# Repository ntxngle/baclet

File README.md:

# baclet
## What and Why

A mobile, battery powered trinket that measures BAC (Blood AlcoholContent) by tracking time and drinks you enter via the extraordinarly user friendly triple button system.

Obviously this is not a medical device. You input body params on setup, then can log each drink by volume and percentage, and it calculates BAC. It has chargering, a buzzer, USB serial, and a nice 1.28 OLED, all behind an auto-off switch to save power.

Being the science minded individual I am, I have always approached consumption of this nature from a data driven mindset: I logged, sometimes more honestly than others, my drinks, and monitored my BAC level in the app. While I wouldn't say this pastime is exactly a hobby or passion, it's a part of my life and I figured it would be fun to try to connect the two disciplines. Thats why I made this brilliant contraption.

## Photos

## How it works
Again to be clear this is not a breathalyzer. You enter the drinks manually. Then, based parameters you've entered like weight, gender, it calculates the BAC level via the widmark formula. 

Drink inputs are timestamped from RTC and put into flash storage so it can be access and included in calculations on wake.

It was designed to be a thin as possible, with all SMD compontents located on one side, and the screen and buttons on the other. Barring the battery, this could have easily been a centimeter wide, but of course I'm not apple and cannot afford a custom designed battery to fit in the free space perfectly. I'm quite proud of the PCB design however, its pretty compact for the time it took me to make.

## BOM
|name                |quantity|Footprint                                         |link                                                |Price|
|--------------------|--------|--------------------------------------------------|----------------------------------------------------|-----|
|PCB                 |1       |                                                  |JLC files in repo                                   |2    |
|Battery             |1       |                                                  |https://es.aliexpress.com/item/1005012320035574.html|6    |
|Case                |1       |                                                  |3d print it                                         |1    |
|PCF8523T            |1       |SOIC-8_3.9x4.9mm_P1.27mm                          |https://www.lcsc.com/product-detail/C2651516.html   |1.19 |
|100k                |8       |R_0603_1608Metric                                 |https://www.lcsc.com/product-detail/C2906980.html   |0.38 |
|RP2040              |1       |QFN-56-1EP_7x7mm_P0.4mm_EP3.2x3.2mm               |https://www.lcsc.com/product-detail/C2040.html      |0.99 |
|1N4148              |3       |D_SOD-323F                                        |https://www.lcsc.com/product-detail/C2128.html      |0.59 |
|TPS63900            |1       |WSON-10-1EP_2.5x2.5mm_P0.5mm_EP1.2x2mm_ThermalVias|https://www.lcsc.com/product-detail/C1518762.html   |1.21 |
|W25Q32JVSS          |1       |SOIC-8_5.3x5.3mm_P1.27mm                          |https://www.lcsc.com/product-detail/C179173.html    |2.49 |
|NPN C22400355       |4       |SOT-23                                            |https://www.lcsc.com/product-detail/C22400355.html  |0.55 |
|2169900002          |1       |USB-SMD_2169900002                                |https://www.lcsc.com/product-detail/C3197869.html   |1.38 |
|2.2uH SRN3015TA-2R2M|1       |L_APV_ANR3010                                     |https://www.lcsc.com/product-detail/C5362464.html   |0.61 |
|C20625731           |1       |Crystal_SMD_3225-4Pin_3.2x2.5mm                   |https://www.lcsc.com/product-detail/C20625731.html  |1.47 |
|USBLC6-2SC6         |1       |SOT-23-6                                          |https://www.lcsc.com/product-detail/C7519.html      |0.87 |
|MLT-5020            |1       |BUZ-SMD_L5.0-W5.5-P4.60                           |https://www.lcsc.com/product-detail/C94598.html     |0.44 |
|MCP73831-2-OT       |1       |SOT-23-5                                          |https://www.lcsc.com/product-detail/C635037.html    |1.58 |
|B3F-1052            |3       |KEY-TH_4P-L6.0-W6.0-P4.50                         |https://www.lcsc.com/product-detail/C87037.html     |0.92 |
|HS13L03W2C01        |1       |OLED-TH_L35.4-W33.5_HS13L03W2C01                  |https://www.lcsc.com/product-detail/C7465997.html   |4.98 |
|Total               |        |                                                  |                                                    |32.54|

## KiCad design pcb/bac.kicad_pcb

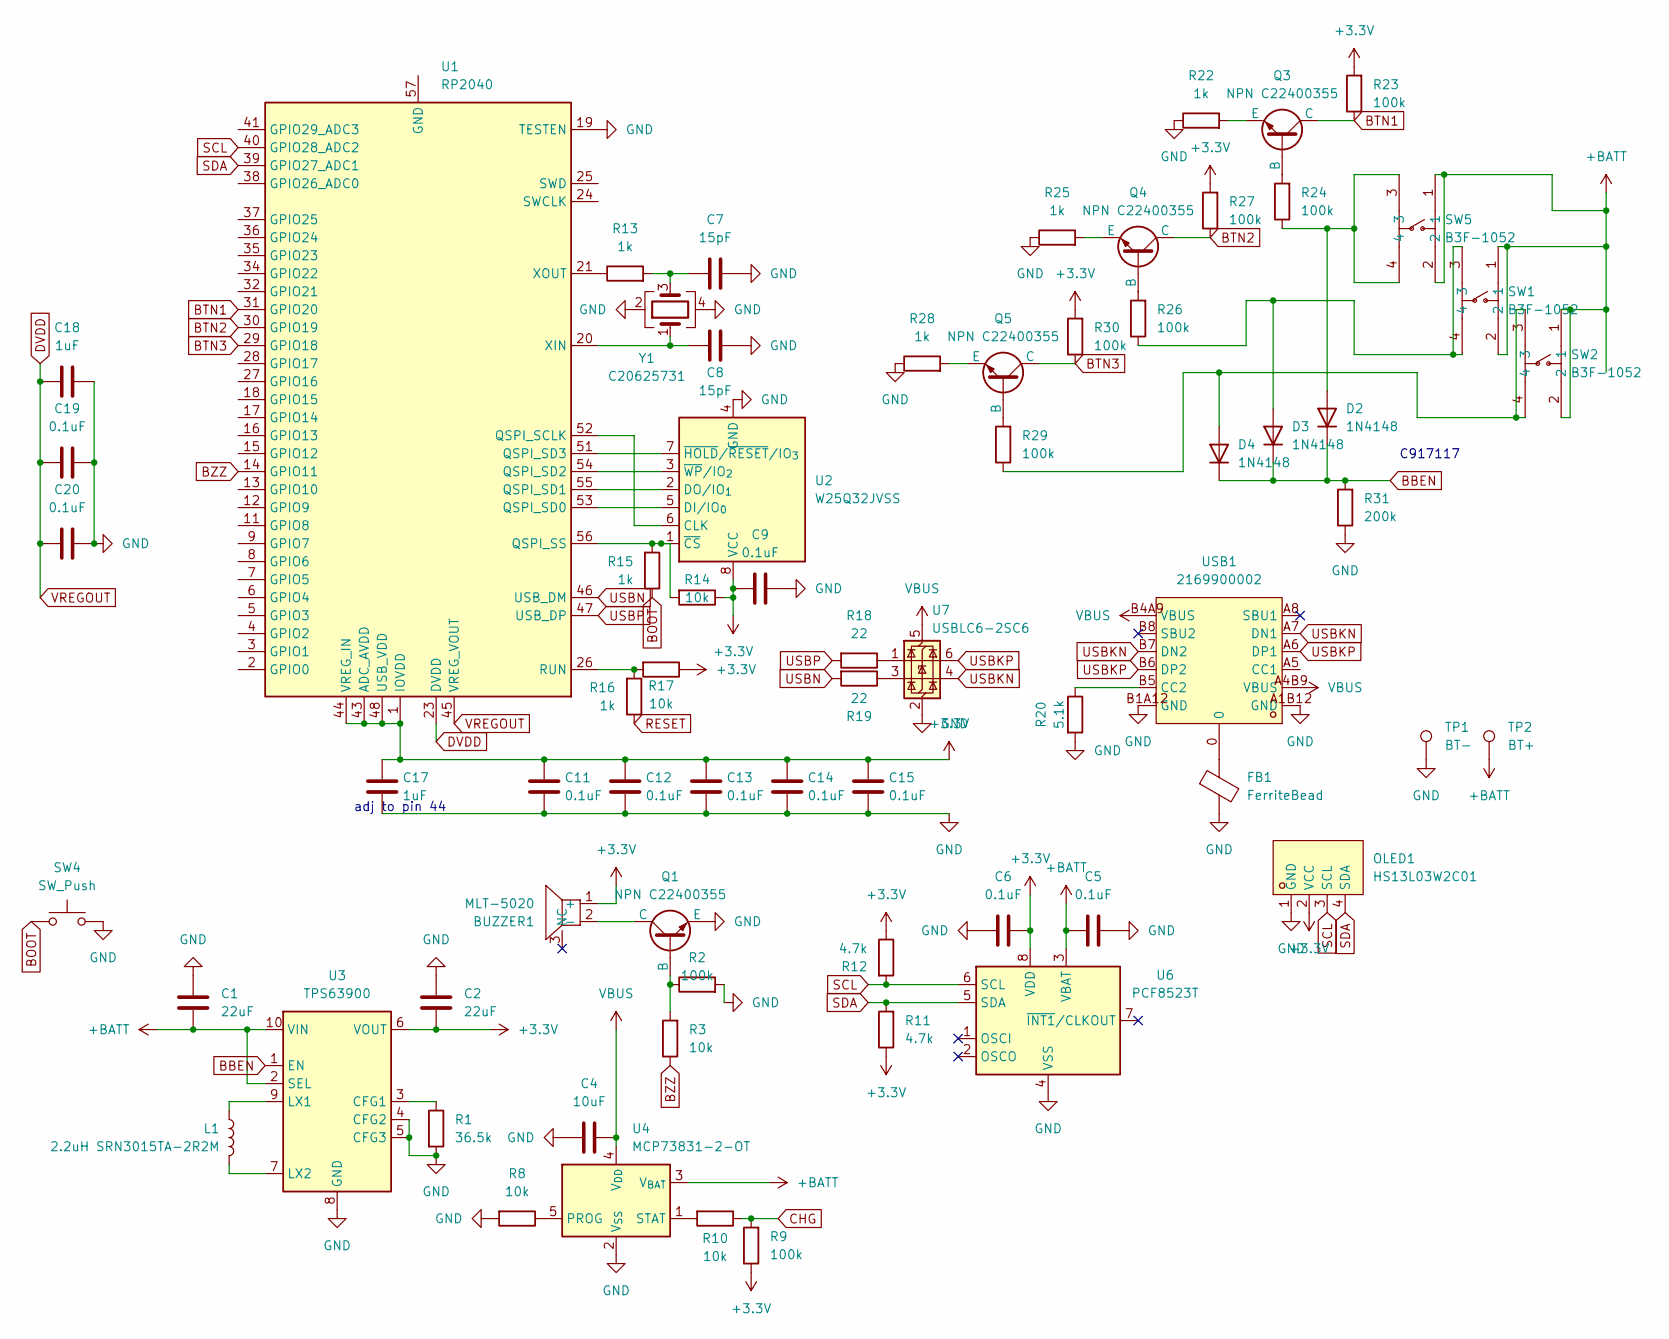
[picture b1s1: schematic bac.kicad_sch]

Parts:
BUZZER1: MLT-5020; BUZ-SMD_L5.0-W5.5-P4.60; MPN MLT-5020; LCSC Part C94598
C1, C2: 22uF; C_0603_1608Metric
C4: 10uF; C_0603_1608Metric
C5, C6, C9, C11, C12, C13, C14, C15, C19, C20: 0.1uF; C_0603_1608Metric
C7, C8: 15pF; C_0603_1608Metric
C17, C18: 1uF; C_0603_1608Metric
D2, D3, D4: 1N4148; D_SOD-323F
FB1: FerriteBead; L_0603_1608Metric
L1: 2.2uH SRN3015TA-2R2M; L_APV_ANR3010
OLED1: HS13L03W2C01; OLED-TH_L35.4-W33.5_HS13L03W2C01; MPN HS13L03W2C01; LCSC Part C7465997
Q1, Q3, Q4, Q5: NPN C22400355; SOT-23
R1: 36.5k; R_0603_1608Metric
R2, R9, R23, R24, R26, R27, R29, R30: 100k; R_0603_1608Metric
R3, R8, R10, R14, R17: 10k; R_0603_1608Metric
R11, R12: 4.7k; R_0603_1608Metric
R13, R15, R16, R22, R25, R28: 1k; R_0603_1608Metric
R18, R19: 22; R_0603_1608Metric
R20: 5.1k; R_0603_1608Metric
R31: 200k; R_0603_1608Metric
SW1, SW2, SW5: B3F-1052; KEY-TH_4P-L6.0-W6.0-P4.50; MPN B3F-1052; LCSC Part C87037
SW4: SW_Push
TP1: BT-; TestPoint_THTPad_2.0x2.0mm_Drill1.0mm
TP2: BT+; TestPoint_THTPad_2.0x2.0mm_Drill1.0mm
U1: RP2040; QFN-56-1EP_7x7mm_P0.4mm_EP3.2x3.2mm
U2: W25Q32JVSS; SOIC-8_5.3x5.3mm_P1.27mm
U3: TPS63900; WSON-10-1EP_2.5x2.5mm_P0.5mm_EP1.2x2mm_ThermalVias
U4: MCP73831-2-OT; SOT-23-5
U6: PCF8523T; SOIC-8_3.9x4.9mm_P1.27mm
U7: USBLC6-2SC6; SOT-23-6
USB1: 2169900002; USB-SMD_2169900002; MPN 2169900002; LCSC Part C3197869
Y1: C20625731; Crystal_SMD_3225-4Pin_3.2x2.5mm

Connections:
+3.3V: BUZZER1.1 (+), C2.1, C6.1, C9.2, C11.1, C12.1, C13.1, C14.1, C15.1, C17.1, OLED1.2 (VCC), R9.1, R11.1, R12.1, R14.1, R17.1, R23.2, R27.2, R30.2, U1.1 (IOVDD), U1.10 (IOVDD), U1.22 (IOVDD), U1.33 (IOVDD), U1.42 (IOVDD), U1.43 (ADC_AVDD), U1.44 (VREG_IN), U1.48 (USB_VDD), U1.49 (IOVDD), U2.8 (VCC), U3.6 (VOUT), U6.8 (VDD)
+BATT: C1.1, C5.2, SW1.1, SW1.2, SW2.1, SW2.2, SW5.1, SW5.2, TP2.1, U3.2 (SEL), U3.10 (VIN), U4.3 (V_{BAT}), U6.3 (VBAT)
BBEN: D2.1 (K), D3.1 (K), D4.1 (K), R31.2, U3.1 (EN)
BOOT: R15.1, SW4.1
BTN1: Q3.1 (C), R23.1, U1.31 (GPIO20)
BTN2: Q4.1 (C), R27.1, U1.30 (GPIO19)
BTN3: Q5.1 (C), R30.1, U1.29 (GPIO18)
BZZ: R3.1, U1.14 (GPIO11)
CHG: R9.2, R10.1
DVDD: C18.2, C19.2, C20.2, U1.23 (DVDD), U1.45 (VREG_VOUT), U1.50 (DVDD)
GND: C1.2, C2.2, C4.2, C5.1, C6.2, C7.1, C8.1, C9.1, C11.2, C12.2, C13.2, C14.2, C15.2, C17.2, C18.1, C19.1, C20.1, FB1.2, OLED1.1 (GND), Q1.3 (E), R1.2, R2.2, R8.2, R20.2, R22.1, R25.1, R28.1, R31.1, SW4.2, TP1.1, U1.19 (TESTEN), U2.4 (GND), U3.4 (CFG2), U3.5 (CFG3), U3.8 (GND), U3.11 (GND), U4.2 (V_{SS}), U6.4 (VSS), U7.2 (GND), USB1.A1B12 (GND), USB1.B1A12 (GND), Y1.2, Y1.4
unnamed: BUZZER1.2 (-), Q1.1 (C)
unnamed: C7.2, R13.2, Y1.3
unnamed: D2.2 (A), R24.1, SW5.3, SW5.4
unnamed: D3.2 (A), R26.1, SW1.3, SW1.4
unnamed: D4.2 (A), R29.1, SW2.3, SW2.4
unnamed: FB1.1, USB1.0
unnamed: Q1.2 (B), R2.1, R3.2
unnamed: Q3.2 (B), R24.2
unnamed: Q3.3 (E), R22.2
unnamed: Q4.2 (B), R26.2
unnamed: Q4.3 (E), R25.2
unnamed: Q5.2 (B), R29.2
unnamed: Q5.3 (E), R28.2
unnamed: R18.1, U7.1 (I/O1)
unnamed: R19.1, U7.3 (I/O2)
unnamed: U1.52 (QSPI_SCLK), U2.6 (CLK)
unnamed: U1.53 (QSPI_SD0), U2.5 (DI/IO_{0})
unnamed: U1.55 (QSPI_SD1), U2.2 (DO/IO_{1})
unnamed: U1.54 (QSPI_SD2), U2.3 (~WP/IO_{2})
unnamed: U1.51 (QSPI_SD3), U2.7 (~HOLD/~RESET/IO_{3})
unnamed: R14.2, R15.2, U1.56 (QSPI_SS), U2.1 (~CS)
unnamed: R16.2, R17.2, U1.26 (RUN)
unnamed: C8.2, U1.20 (XIN), Y1.1
unnamed: R13.1, U1.21 (XOUT)
unnamed: R1.1, U3.3 (CFG1)
unnamed: L1.2, U3.9 (LX1)
unnamed: L1.1, U3.7 (LX2)
unnamed: R8.1, U4.5 (PROG)
unnamed: R10.2, U4.1 (STAT)
unnamed: R20.1, USB1.B5 (CC2)
RESET: R16.1
SCL: OLED1.3 (SCL), R12.2, U1.40 (GPIO28_ADC2), U6.6 (SCL)
SDA: OLED1.4 (SDA), R11.2, U1.39 (GPIO27_ADC1), U6.5 (SDA)
USBKN: U7.4 (I/O2), USB1.A7 (DN1), USB1.B7 (DN2)
USBKP: U7.6 (I/O1), USB1.A6 (DP1), USB1.B6 (DP2)
USBN: R19.2, U1.46 (USB_DM)
USBP: R18.2, U1.47 (USB_DP)
VBUS: C4.1, U4.4 (V_{DD}), U7.5 (VBUS), USB1.A4B9 (VBUS), USB1.B4A9 (VBUS)

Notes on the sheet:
adj to pin 44
C917117

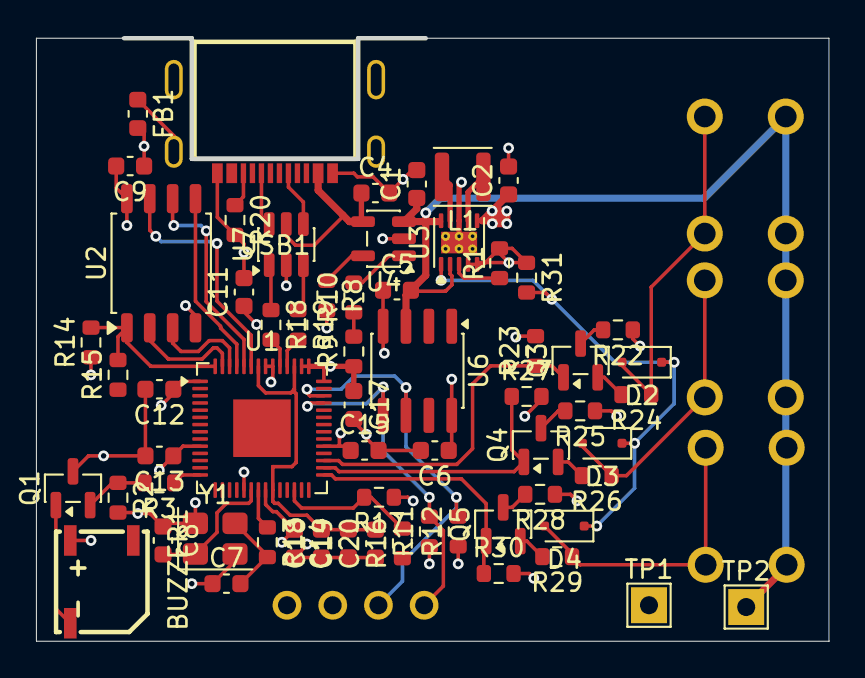
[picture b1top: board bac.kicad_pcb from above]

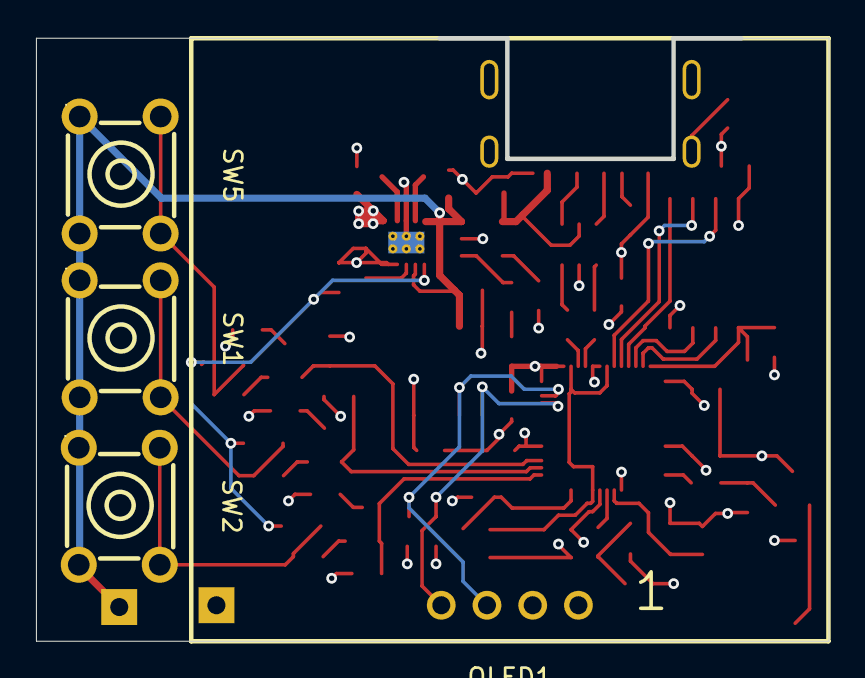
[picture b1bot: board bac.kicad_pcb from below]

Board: 4 copper layers, 43.8 x 33.4 mm, 67 parts (4 on the bottom side), 47 nets.

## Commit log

2026-06-26 larp
